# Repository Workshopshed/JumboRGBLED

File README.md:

# Jumbo RGB LED
A giant sized RGB LED using 10W COB LEDs and a WS2811 driver chip.

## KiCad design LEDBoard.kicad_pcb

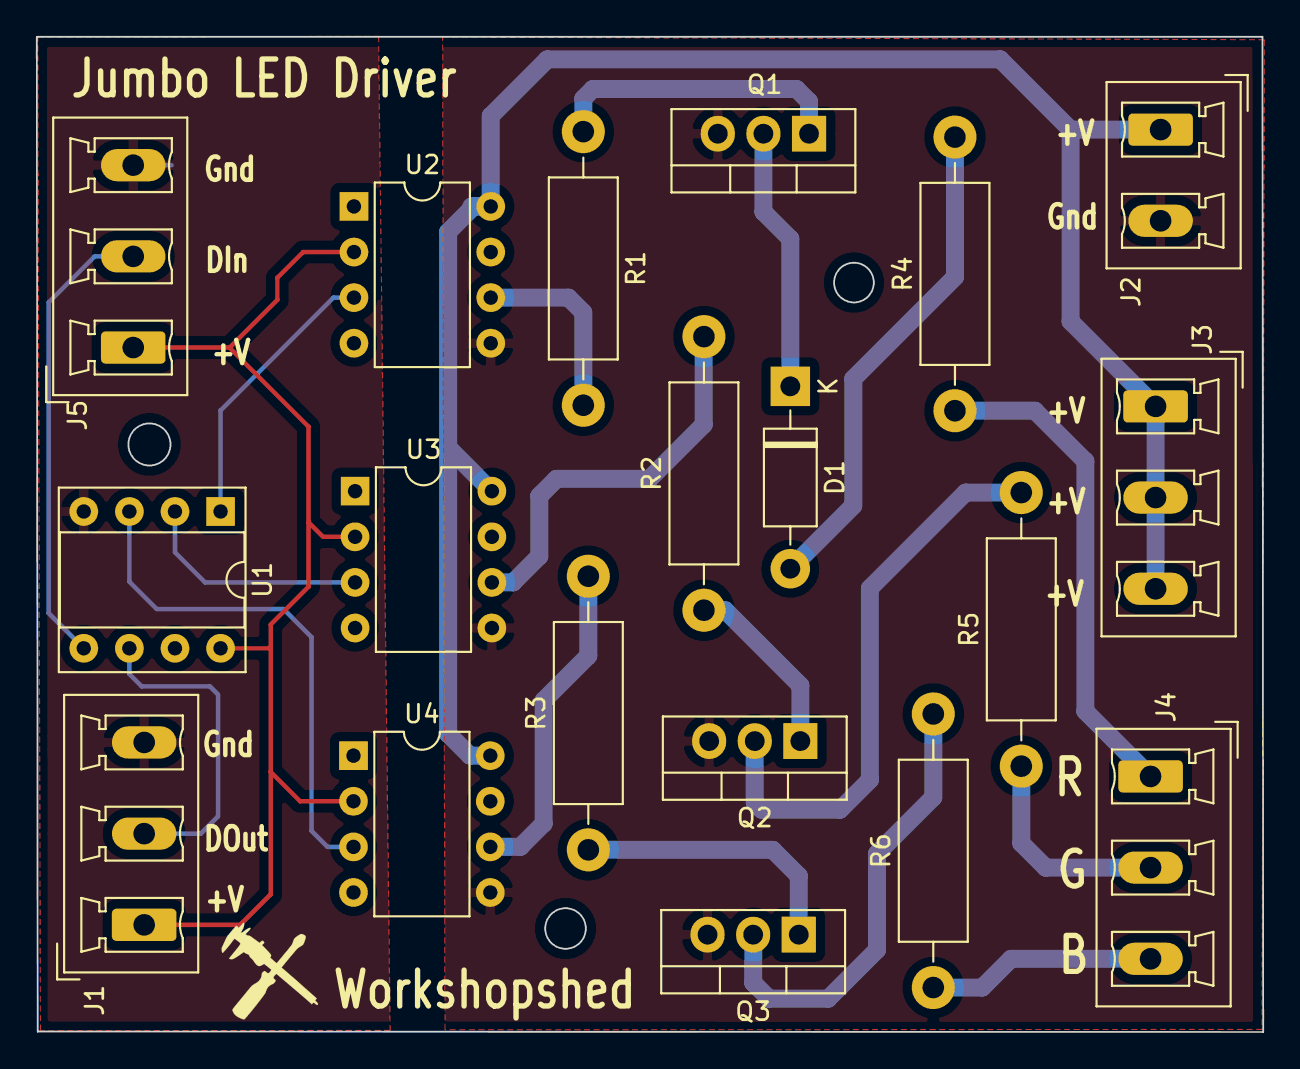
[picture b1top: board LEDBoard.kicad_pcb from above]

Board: 2 copper layers, 68.3 x 55.4 mm, 20 parts (0 on the bottom side), 22 nets.

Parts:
 : Logo
D1: 1N4001; D_DO-41_SOD81_P10.16mm_Horizontal
J1, J3, J4: Screw_Terminal_01x03; PhoenixContact_MCV_1,5_3-G-5.08_1x03_P5.08mm_Vertical
J2: Screw_Terminal_01x02; PhoenixContact_MCV_1,5_2-G-5.08_1x02_P5.08mm_Vertical
J5: Conn_01x03_Male; PhoenixContact_MCV_1,5_3-G-5.08_1x03_P5.08mm_Vertical
Q1, Q2, Q3: IRL7833; TO-220-3_Vertical
R1, R2, R3: 100R; R_Axial_DIN0411_L9.9mm_D3.6mm_P15.24mm_Horizontal
R4, R5, R6: R7.6; R_Axial_DIN0411_L9.9mm_D3.6mm_P15.24mm_Horizontal
U1: WS2811; DIP-8_W7.62mm_Socket
U2, U3, U4: HCPL-3120; DIP-8_W7.62mm

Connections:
+5V: J1.1, J5.1, U1.8, U2.2, U3.2, U4.2
+15V: J2.1, J3.1, J3.2, J3.3, U2.8, U3.8, U4.8
GND: J2.2, Q1.3, Q2.3, Q3.3, U2.5, U3.5, U4.5
GNDD: J1.3, J5.3, U1.4
unnamed: D1.1, Q1.2
unnamed: D1.2, R4.2
unnamed: J1.2, U1.6
unnamed: J4.1, R4.1
unnamed: J4.2, R5.1
unnamed: J4.3, R6.1
unnamed: J5.2, U1.5
unnamed: Q1.1, R1.1
unnamed: Q2.1, R2.1
unnamed: Q2.2, R5.2
unnamed: Q3.1, R3.1
unnamed: Q3.2, R6.2
unnamed: R1.2, U2.6
unnamed: R2.2, U3.6
unnamed: R3.2, U4.6
unnamed: U1.1, U2.3
unnamed: U1.2, U3.3
unnamed: U1.3, U4.3

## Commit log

2021-12-19 Models
2022-01-15 Arduino Uno Tray
